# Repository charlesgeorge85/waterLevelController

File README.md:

# Water Level Controller for Home

This project implements a smart water tank pump controller using an ESP32 microcontroller. It manages the transfer of water between an Underground Tank (UGT) and an Overhead Tank (OHT), ensuring safe, efficient operation with dry-run protection and a web interface for monitoring and manual control.

## 1. Problem Statement

The system is designed to automatically control a water pump to transfer water from a UGT to an OHT. Key challenges addressed include:

- Preventing pump operation when UGT is empty (dry run).
- Automating pump ON/OFF based on OHT and UGT water levels.
- Providing manual mode, switch is set to manual, in manual mode, pump will be 'on', so thts pump can be controlled via main power switch

## 1.1 Tank Level Thresholds

- **Overhead Tank (OHT):**
  - `OHT_FULL`: Tank is full.
  - `OHT_EMPTY`: Tank is empty.

- **Underground Tank (UGT):**
  - `UGT_EMPTY`: Tank is empty.
  - `UGT_NOT_EMPTY`: Tank has sufficient water.

## 2. Use Cases

### 2.1 Pump Activation

The pump is activated when:
- OHT level is below `OHT_EMPTY`.
- UGT level is above `UGT_EMPTY`.

### 2.2 Pump Deactivation

The pump is turned off when:
- OHT reaches `OHT_FULL`, or
- UGT falls below `UGT_EMPTY`, or
- A dry-run condition is detected.

If deactivation is due to UGT low level, the pump will only reactivate once UGT is above `UGT_NOT_EMPTY`.

### 2.3 Dry Run Detection & Handling

- Dry-run is detected via motor current using a Current Transformer (CT).
- For a 0.25 HP motor, current < 0.8 A indicates a dry run, during normal run, the measured current is 1.27A
- On dry run:
  - A buzzer alerts.
  - Alarm can be cleared with a Alarm reset switch
  
## 3. Hardware Implementation

- **Controller**: ESP32
- **Features**:
  - Water level monitoring (UGT & OHT)
  - Motor control (auto/manual)
  - Current sensing
  - Configurable dry-run threshold
  - Web UI for (future Plan):
    - Displaying water levels
    - Manual motor control
    - Viewing current consumption
    - Threshold configuration

## 4. Web UI(future Plan)

A web-based interface hosted on ESP32 allows real-time visualization and control of the pump system.

## 5. ESP32 Devkit V1 details

[ESP32 DOIT DevKit V1 Board Details](https://www.espboards.dev/esp32/esp32doit-devkit-v1/)

---

### Author
Joseph George

### License
This project is open-source and available under the [MIT License](LICENSE).

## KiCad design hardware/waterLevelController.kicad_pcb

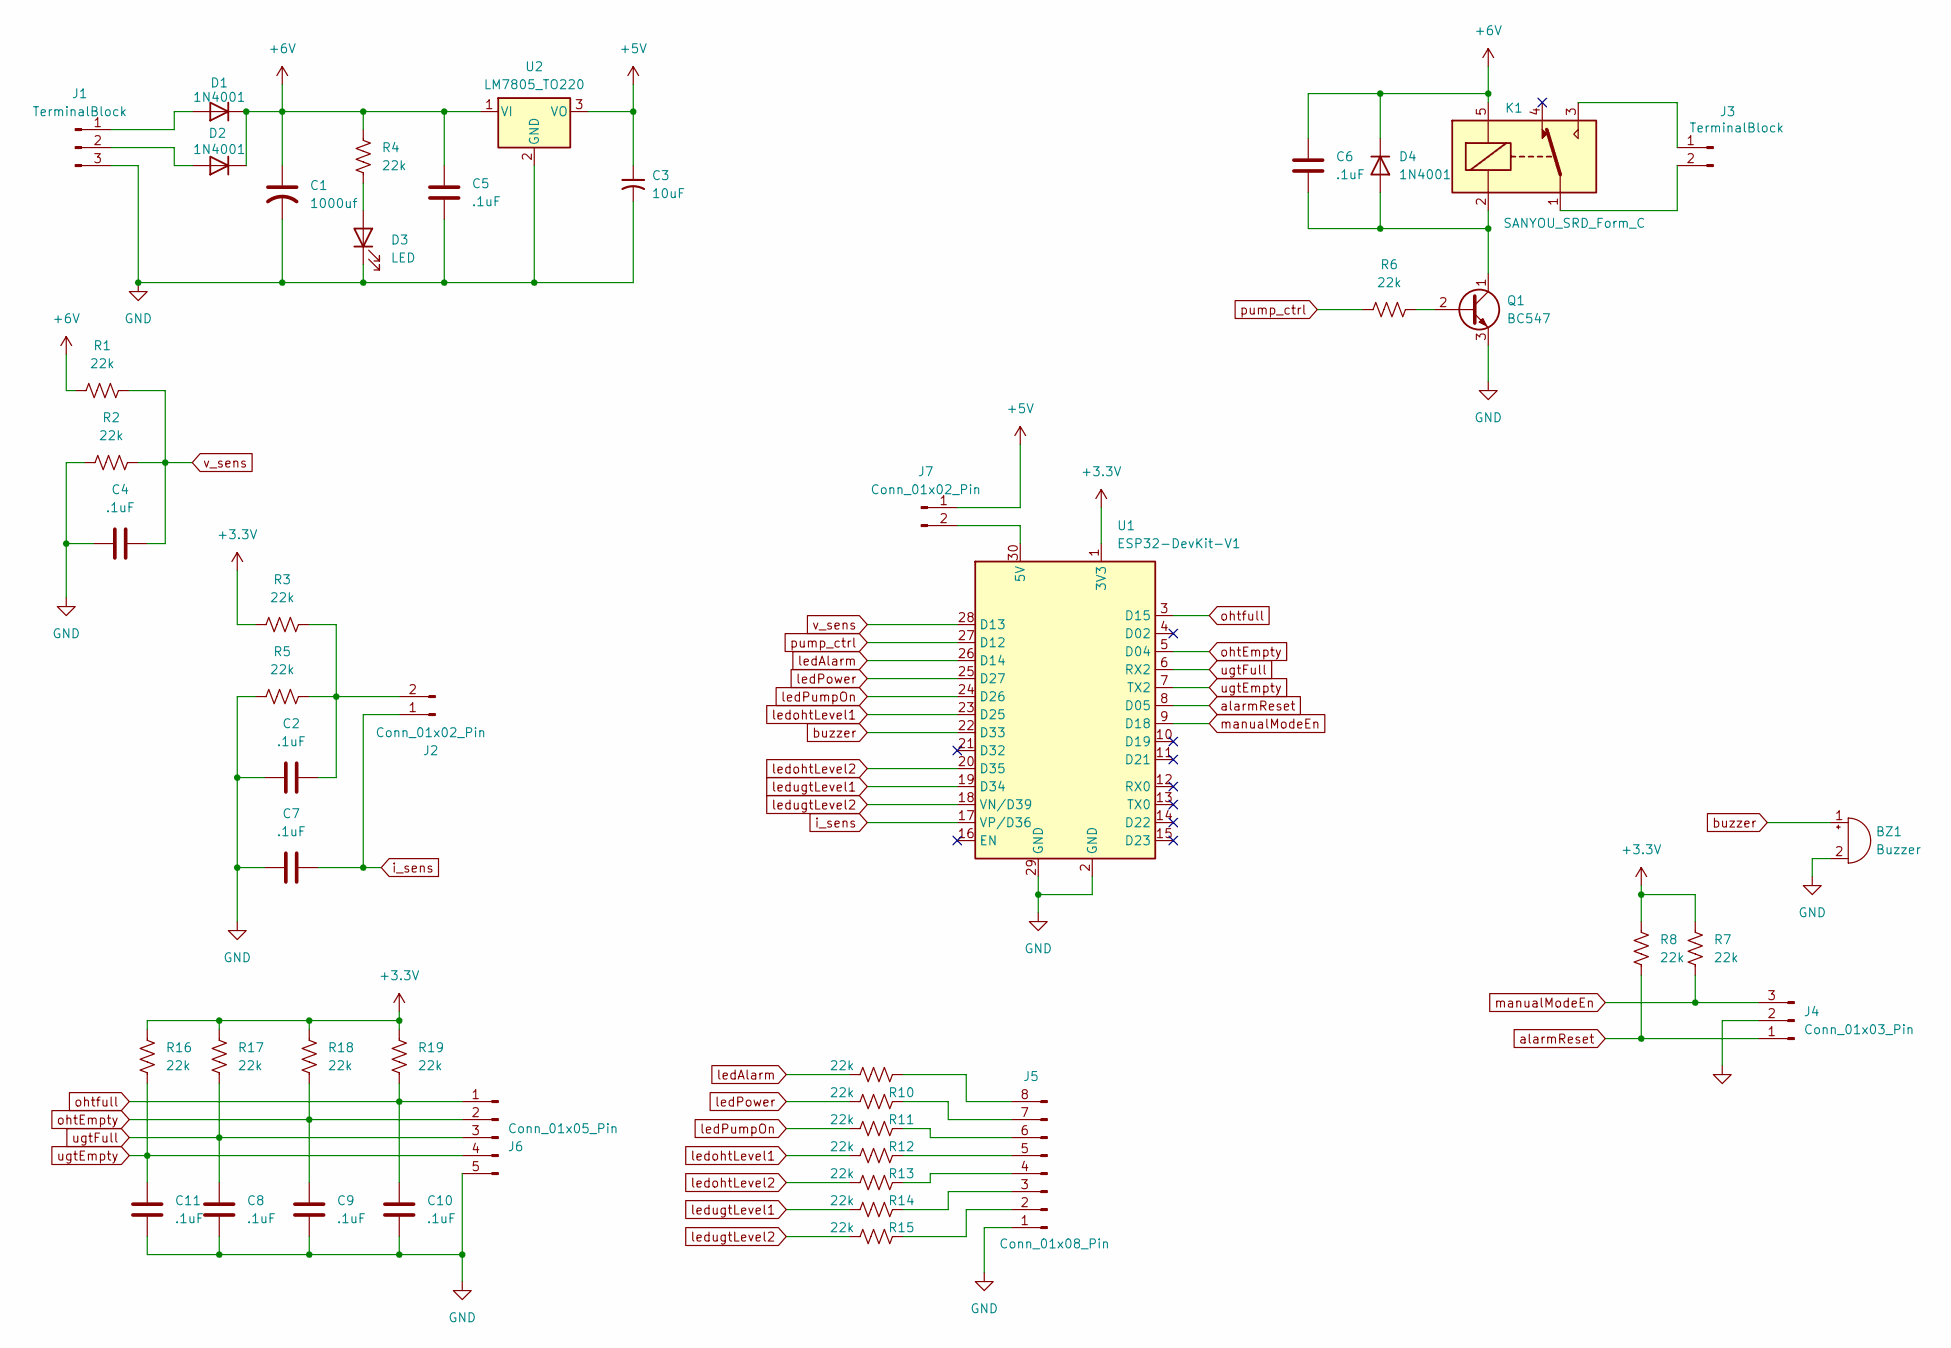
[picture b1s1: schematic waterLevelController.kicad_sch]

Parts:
BZ1: Buzzer; BUZ_12X7P6
C1: 1000uf; C_Radial_D12.5mm_H20.0mm_P5.00mm
C2, C4, C5, C6, C7, C8, C9, C10, C11: .1uF; C_Disc_D3.8mm_W2.6mm_P2.50mm
C3: 10uF; CP_Radial_D8.0mm_P2.50mm
D1, D2, D4: 1N4001; D_DO-41_SOD81_P10.16mm_Horizontal
D3: LED; LED_D3.0mm
J1: TerminalBlock; PhoenixContact_MCV_1,5_3-G-3.81_1x03_P3.81mm_Vertical
J2, J7: Conn_01x02_Pin; PinHeader_1x02_P2.54mm_Vertical
J3: TerminalBlock; PhoenixContact_MCV_1,5_2-G-3.81_1x02_P3.81mm_Vertical
J4: Conn_01x03_Pin; PinHeader_1x03_P2.54mm_Vertical
J5: Conn_01x08_Pin; PinHeader_1x08_P2.54mm_Vertical
J6: Conn_01x05_Pin; PhoenixContact_MCV_1,5_5-G-3.81_1x05_P3.81mm_Vertical
K1: SANYOU_SRD_Form_C; Relay_SPDT_SANYOU_SRD_Series_Form_C
Q1: BC547; TO-92_Wide
R1, R2, R3, R4, R5, R6, R7, R8, R9, R10, R11, R12, R13, R14, R15, R16, R17, R18, R19: 22k; R_Axial_DIN0309_L9.0mm_D3.2mm_P5.08mm_Vertical
U1: ESP32-DevKit-V1
U2: LM7805_TO220; TO-220-3_Vertical

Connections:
+3.3V: R3.1, R7.2, R8.2, R16.1, R17.1, R18.1, R19.1, U1.1 (3V3)
+5V: C3.1, J7.1, U2.3 (VO)
+6V: C1.1, C5.2, C6.2, D1.1 (K), D2.1 (K), D4.1 (K), K1.5, R1.1, R4.1, U2.1 (VI)
GND: BZ1.2 (-), C1.2, C2.1, C3.2, C4.1, C5.1, C7.1, C8.2, C9.2, C10.2, C11.2, D3.1 (K), J1.3, J4.2, J5.1, J6.5, Q1.3 (E), R2.1, R5.1, U1.2 (GND), U1.29 (GND), U2.2 (GND)
unnamed: D1.2 (A), J1.1
unnamed: D2.2 (A), J1.2
unnamed: D3.2 (A), R4.2
unnamed: C6.1, D4.2 (A), K1.2, Q1.1 (C)
unnamed: C2.2, J2.2, R3.2, R5.2
unnamed: J3.1, K1.3
unnamed: J3.2, K1.1
unnamed: J5.2, R15.1
unnamed: J5.3, R14.1
unnamed: J5.4, R13.1
unnamed: J5.5, R12.1
unnamed: J5.6, R11.1
unnamed: J5.7, R10.1
unnamed: J5.8, R9.1
unnamed: J7.2, U1.30 (5V)
unnamed: Q1.2 (B), R6.2
alarmReset: J4.1, R8.1, U1.8 (D05)
buzzer: BZ1.1 (+), U1.22 (D33)
i_sens: C7.2, J2.1, U1.17 (VP/D36)
ledAlarm: R9.2, U1.26 (D14)
ledPower: R10.2, U1.25 (D27)
ledPumpOn: R11.2, U1.24 (D26)
ledohtLevel1: R12.2, U1.23 (D25)
ledohtLevel2: R13.2, U1.20 (D35)
ledugtLevel1: R14.2, U1.19 (D34)
ledugtLevel2: R15.2, U1.18 (VN/D39)
manualModeEn: J4.3, R7.1, U1.9 (D18)
ohtEmpty: C9.1, J6.2, R18.2, U1.5 (D04)
ohtfull: C10.1, J6.1, R19.2, U1.3 (D15)
pump_ctrl: R6.1, U1.27 (D12)
ugtEmpty: C11.1, J6.4, R16.2, U1.7 (TX2)
ugtFull: C8.1, J6.3, R17.2, U1.6 (RX2)
v_sens: C4.2, R1.2, R2.2, U1.28 (D13)

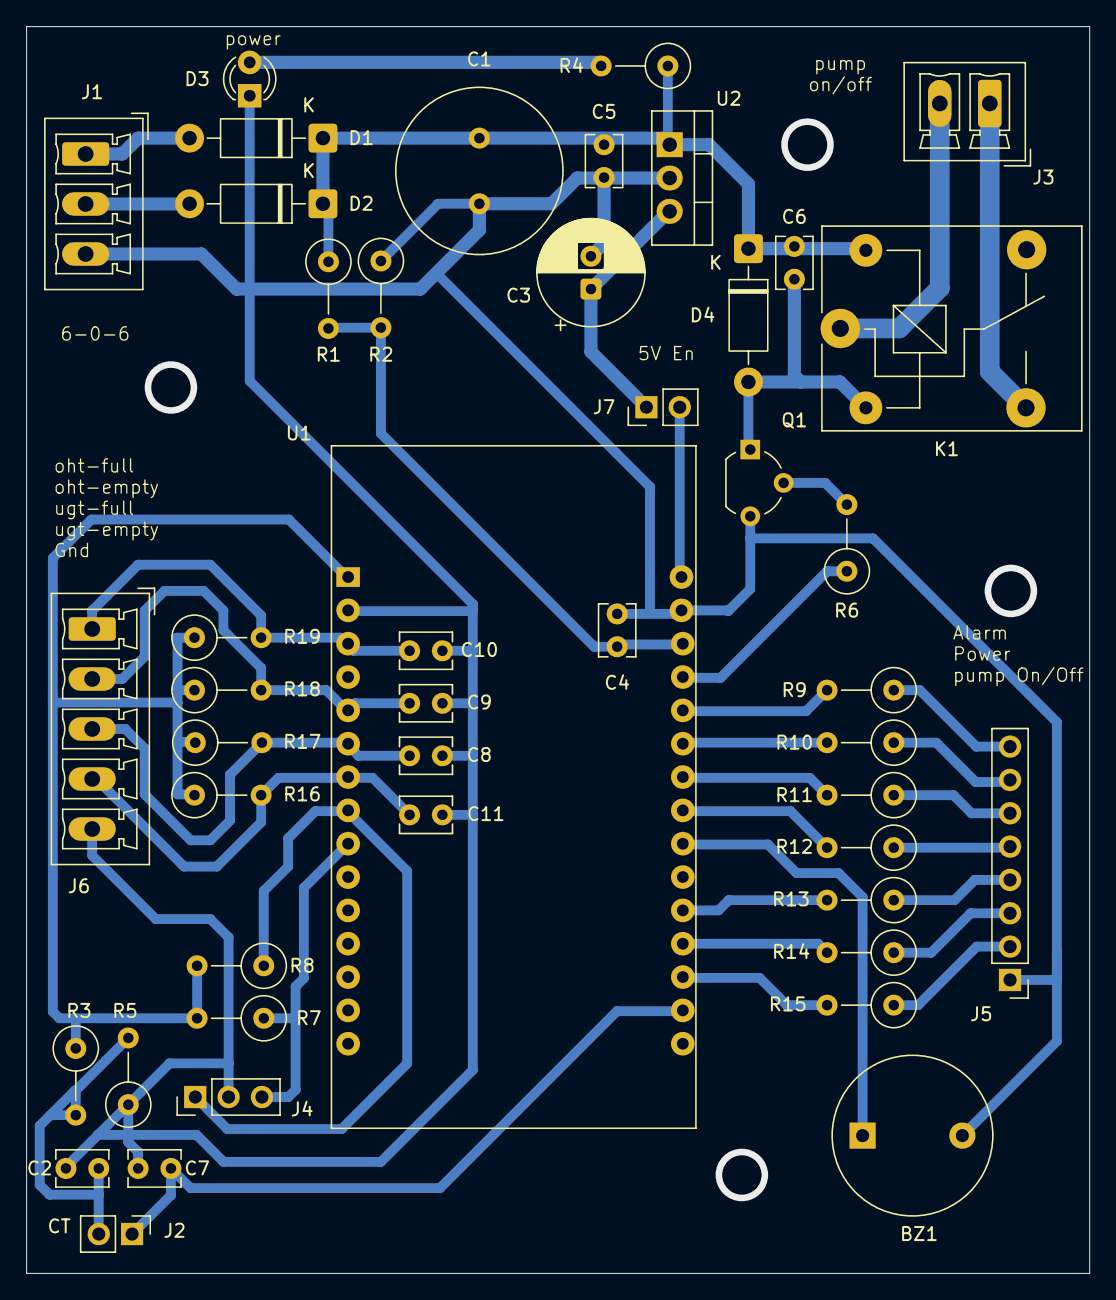
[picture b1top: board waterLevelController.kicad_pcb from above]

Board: 2 copper layers, 81.0 x 95.0 mm, 46 parts (0 on the bottom side), 37 nets.

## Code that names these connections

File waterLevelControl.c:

#include <Arduino.h>

// GPIO Pin Definitions
#define OHT_FULL_PIN        15
#define OHT_EMPTY_PIN       02
#define UGT_EMPTY_PIN       04
#define UGT_NOT_EMPTY_PIN   16
#define PUMP_CONTROL_PIN    34
#define CURRENT_SENSOR_PIN  33
#define BUZZER_PIN          33
#define ALARM_CLEAR_PIN     27
#define MANUAL_MODE_SWITCH  14

// Dry-run thresholds (with optional hysteresis)
#define DRY_RUN_CURRENT_THRESHOLD   2.0  // Trigger below this
#define DRY_RUN_RECOVERY_THRESHOLD  2.5  // Reset above this

// Dry-run delay before checking (after pump ON)
const unsigned long DRY_RUN_DELAY_MS = 2 * 60 * 1000; // 2 minutes
const unsigned long DRY_RUN_BUZZ_INTERVAL = 30 * 60 * 1000; // 30 mins

// System States
bool pumpOn = false;
bool manualMode = false;
bool dryRunDetected = false;
bool ugtPreviouslyEmpty = false;

unsigned long lastDryRunBuzzTime = 0;
unsigned long pumpStartTime = 0;

void setup() {
  Serial.begin(115200);

  // Sensor Inputs
  pinMode(OHT_FULL_PIN, INPUT);
  pinMode(OHT_EMPTY_PIN, INPUT);
  pinMode(UGT_EMPTY_PIN, INPUT);
  pinMode(UGT_NOT_EMPTY_PIN, INPUT);

  // Control Outputs
  pinMode(PUMP_CONTROL_PIN, OUTPUT);
  pinMode(BUZZER_PIN, OUTPUT);

  // User Inputs
  pinMode(ALARM_CLEAR_PIN, INPUT_PULLUP);
  pinMode(MANUAL_MODE_SWITCH, INPUT_PULLUP);

  digitalWrite(PUMP_CONTROL_PIN, LOW);
  digitalWrite(BUZZER_PIN, LOW);
}

bool readSensor(int pin) {
  return digitalRead(pin) == LOW; // Assume LOW means "active"
}

float readCurrent() {
  int adcValue = analogRead(CURRENT_SENSOR_PIN);
  float current = ((float)adcValue / 4095.0) * 5.0; // Simulated conversion
  return current;
}

void activatePump() {
  if (!pumpOn) {
    digitalWrite(PUMP_CONTROL_PIN, HIGH);
    pumpOn = true;
    pumpStartTime = millis();
    Serial.println("Pump ON");
  }
}

void deactivatePump() {
  if (pumpOn) {
    digitalWrite(PUMP_CONTROL_PIN, LOW);
    pumpOn = false;
    Serial.println("Pump OFF");
  }
}

void handleDryRun() {
  if (!pumpOn) return; // ✅ Only check if pump is running

  unsigned long now = millis();
  if (now - pumpStartTime < DRY_RUN_DELAY_MS) {
    // ✅ Wait 2 minutes before checking
    return;
  }

  float current = readCurrent();

  if (dryRunDetected) {
    if (current > DRY_RUN_RECOVERY_THRESHOLD) {
      dryRunDetected = false;
      Serial.println("Dry run cleared.");
    }
  } else {
    if (current < DRY_RUN_CURRENT_THRESHOLD) {
      dryRunDetected = true;
      deactivatePump();
      Serial.println("Dry run detected.");
    }
  }

  if (dryRunDetected) {
    if (now - lastDryRunBuzzTime > DRY_RUN_BUZZ_INTERVAL) {
      tone(BUZZER_PIN, 1000, 2000); // 2 sec beep
      lastDryRunBuzzTime = now;
    }

    if (digitalRead(ALARM_CLEAR_PIN) == LOW) {
      dryRunDetected = false;
      lastDryRunBuzzTime = 0;
      Serial.println("Dry-run alarm cleared.");
    }
  }
}

void loop() {
  manualMode = digitalRead(MANUAL_MODE_SWITCH) == LOW;

  if (manualMode) {
    Serial.println("Manual Mode Active");
    // Optionally handle pump ON/OFF via buttons here
  } else {
    // Read tank sensor states
    bool ohtEmpty = readSensor(OHT_EMPTY_PIN);
    bool ohtFull = readSensor(OHT_FULL_PIN);
    bool ugtEmpty = readSensor(UGT_EMPTY_PIN);
    bool ugtNotEmpty = readSensor(UGT_NOT_EMPTY_PIN);

    // Track UGT history
    if (ugtEmpty) {
      ugtPreviouslyEmpty = true;
      deactivatePump(); // Safety: prevent dry run
    }

    if (ugtPreviouslyEmpty && ugtNotEmpty) {
      ugtPreviouslyEmpty = false; // Reset lock
    }

    // Normal operation
    if (!manualMode && !dryRunDetected && !ugtPreviouslyEmpty) {
      if (ohtEmpty && !ugtEmpty && !ohtFull) {
        activatePump();
      } else {
        deactivatePump();
      }
    } else {
      deactivatePump();
    }
  }

  // Dry run check (only if pump is ON & delay passed)
  handleDryRun();

  delay(1000);
}

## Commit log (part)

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2025-06-02 Add files via upload
    The main control software
2025-06-03 Readme file updated
2025-06-03 board level sensor validated
2025-06-04 Voltage and Current monitor intergrated in main files
2025-06-04 unwanted print removed
2025-06-06 gpio maping updated as per hardware
2025-06-09 basic functinality validated, IO mapping updated
2025-06-10 HW updation: IO mapping
2025-06-15 1st deployment
2025-06-15 power optmization
2025-06-18 manual mode support added
2025-06-19 manual mode deployed
2025-06-24 Add files via upload
    These are the hardware design files
2025-06-24 Gerber generated Version
2025-06-26 silkscreen updated
2025-06-26 Update README.md
    feature updated
2026-06-06 Convert to PlatformIO C++ project and centralize board configuration
2026-06-07 Update README.md
    esp32 board details added
2026-06-07 Create devkit.jpg
    devkit image added
2026-06-07 Add HW_V2 board pin mapping
2026-06-07 Tune HW_V2 calibration and diagnostics
2026-06-07 Add compile-time debug log gating
